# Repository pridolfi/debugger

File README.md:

# debugger
Simple JTAG debugger based on FT2232H.

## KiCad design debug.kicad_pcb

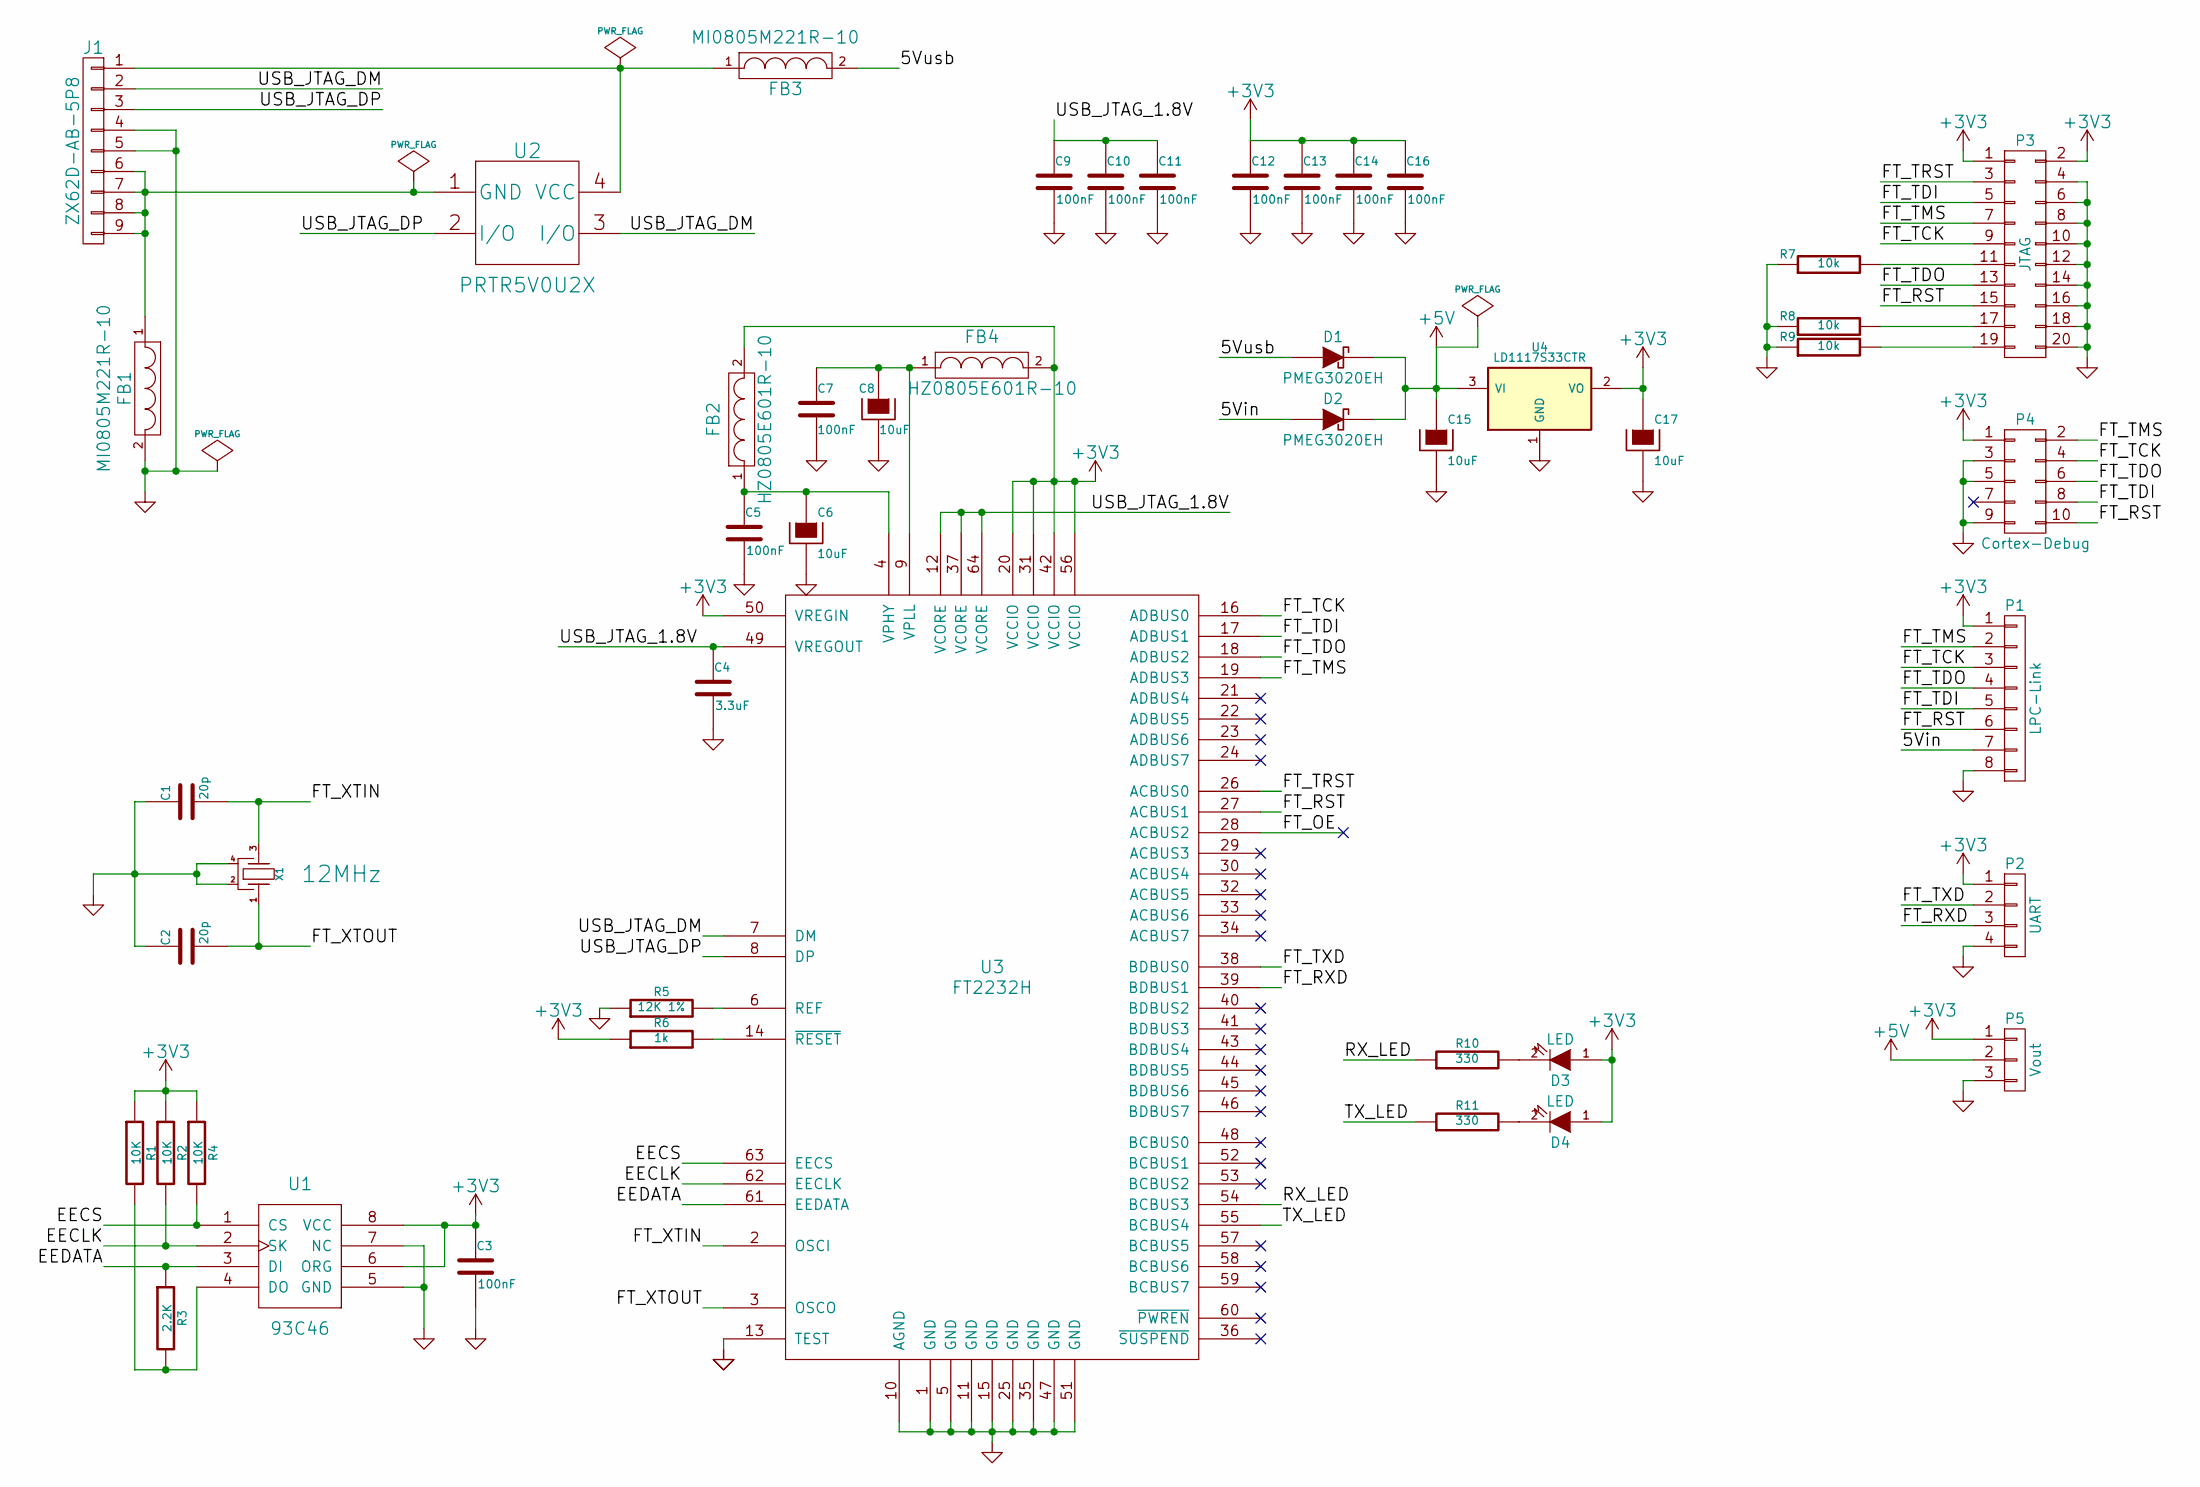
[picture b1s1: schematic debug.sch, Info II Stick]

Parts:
C1, C2: 20p; C_0805_HandSoldering; Digikey 399-8033-1-ND
C3, C5, C7, C9, C10, C11, C12, C13, C14, C16: 100nF; C_0805_HandSoldering; Digikey 399-1167-1-ND
C4: 3.3uF; C_0805_HandSoldering; Digikey 445-7582-1-ND
C6, C8, C15, C17: 10uF; TantalC_SizeA_EIA-3216_HandSoldering; Digikey 399-3525-1-ND
D1, D2: PMEG3020EH; SOD-123
D3, D4: LED; LED-0805
FB1, FB3: MI0805M221R-10; C_0805_HandSoldering; Digikey 240-2392-1-ND
FB2, FB4: HZ0805E601R-10; C_0805_HandSoldering; Digikey 240-2399-1-ND
J1: ZX62D-AB-5P8; USB_microAB_ZX62-AB&B-5PA-11; Digikey H11494CT-ND
P1: LPC-Link; Pin_Header_Straight_1x08
P2: UART; Pin_Header_Straight_1x04
P3: JTAG; Pin_Header_Straight_2x10
P4: Cortex-Debug; Pin_Array_5x2_1.27mm_SMD
P5: Vout; Pin_Header_Straight_1x03
R1, R2, R4: 10K; R_0805_HandSoldering; Digikey P10KACT-ND
R3: 2.2K; R_0805_HandSoldering; Digikey RMCF0805JT2K20CT-ND
R5: 12K 1%; R_0805_HandSoldering; Digikey 311-12.0KCRCT-ND
R6: 1k; R_0805_HandSoldering; Digikey RR12P15.0KDCT-ND
R7, R8, R9: 10k; R_0805_HandSoldering; Digikey 311-12.0KCRCT-ND
R10, R11: 330; R_0805_HandSoldering; Digikey 311-12.0KCRCT-ND
U1: 93C46; -SOIC8; Digikey AT93C46DN-SH-TCT-ND
U2: PRTR5V0U2X; SOT-143B; Digikey 568-4140-1-ND
U3: FT2232H; LQFP64-M05; Digikey 768-1024-1-ND
U4: LD1117S33CTR; SOT223_Opendous
X1: 12MHz; FA238V-XTAL; Digikey/Mouser 887-1831-1-ND

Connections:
+3V3: C3.1, C12.1, C13.1, C14.1, C16.1, C17.1, D3.1 (A), D4.1 (A), FB2.2, FB4.2, P1.1, P2.1, P3.1, P3.2, P4.1, P5.1, R1.1, R2.1, R4.1, R6.1, U1.6 (ORG), U1.8 (VCC), U3.20 (VCCIO), U3.31 (VCCIO), U3.42 (VCCIO), U3.50 (VREGIN), U3.56 (VCCIO), U4.2 (VO)
+5V: C15.1, D1.2 (K), D2.2 (K), P5.2, U4.3 (VI)
/5Vin: D2.1 (A), P1.7
/5Vusb: D1.1 (A), FB3.2
/EECLK: R2.2, U1.2 (SK), U3.62 (EECLK)
/EECS: R4.2, U1.1 (CS), U3.63 (EECS)
/EEDATA: R3.1, U1.3 (DI), U3.61 (EEDATA)
/FT_OE: U3.28 (ACBUS2)
/FT_RST: P1.6, P3.15, P4.10, U3.27 (ACBUS1)
/FT_RXD: P2.3, U3.39 (BDBUS1)
/FT_TCK: P1.3, P3.9, P4.4, U3.16 (ADBUS0)
/FT_TDI: P1.5, P3.5, P4.8, U3.17 (ADBUS1)
/FT_TDO: P1.4, P3.13, P4.6, U3.18 (ADBUS2)
/FT_TMS: P1.2, P3.7, P4.2, U3.19 (ADBUS3)
/FT_TRST: P3.3, U3.26 (ACBUS0)
/FT_TXD: P2.2, U3.38 (BDBUS0)
/FT_XTIN: C1.2, U3.2 (OSCI), X1.3 (B)
/FT_XTOUT: C2.2, U3.3 (OSCO), X1.1 (A)
/RX_LED: R10.1, U3.54 (BCBUS3)
/TX_LED: R11.1, U3.55 (BCBUS4)
/USB_JTAG_1.8V: C4.1, C9.1, C10.1, C11.1, U3.12 (VCORE), U3.37 (VCORE), U3.49 (VREGOUT), U3.64 (VCORE)
/USB_JTAG_DM: J1.2, U2.3 (I/O), U3.7 (DM)
/USB_JTAG_DP: J1.3, U2.2 (I/O), U3.8 (DP)
GND: C1.1, C2.1, C3.2, C4.2, C5.2, C6.2, C7.2, C8.2, C9.2, C10.2, C11.2, C12.2, C13.2, C14.2, C15.2, C16.2, C17.2, FB1.2, J1.4, J1.5, P1.8, P2.4, P3.4, P3.6, P3.8, P3.10, P3.12, P3.14, P3.16, P3.18, P3.20, P4.3, P4.5, P4.9, P5.3, R5.1, R7.1, R8.1, R9.1, U1.5 (GND), U1.7 (NC), U3.1 (GND), U3.5 (GND), U3.10 (AGND), U3.11 (GND), U3.13 (TEST), U3.15 (GND), U3.25 (GND), U3.35 (GND), U3.47 (GND), U3.51 (GND), U4.1 (GND), X1.2 (GND), X1.4 (GND)
unnamed: C5.1, C6.1, FB2.1, U3.4 (VPHY)
unnamed: C7.1, C8.1, FB4.1, U3.9 (VPLL)
unnamed: D3.2 (K), R10.2
unnamed: D4.2 (K), R11.2
unnamed: FB1.1, J1.6, J1.7, J1.8, J1.9, U2.1 (GND)
unnamed: FB3.1, J1.1, U2.4 (VCC)
unnamed: P3.11, R7.2
unnamed: P3.17, R8.2
unnamed: P3.19, R9.2
unnamed: R1.2, R3.2, U1.4 (DO)
unnamed: R5.2, U3.6 (REF)
unnamed: R6.2, U3.14 (~RESET)

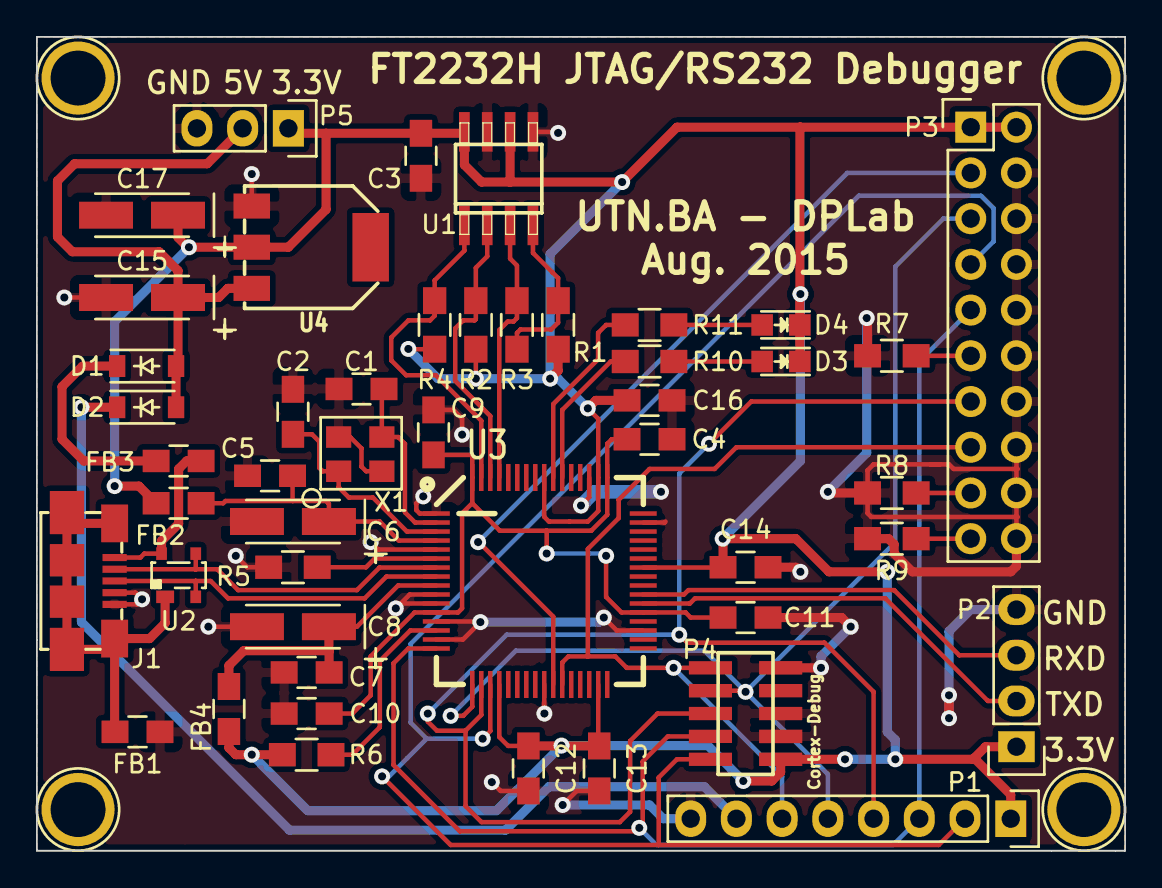
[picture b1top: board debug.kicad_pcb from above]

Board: 2 copper layers, 60.5 x 45.2 mm, 51 parts (0 on the bottom side), 35 nets.

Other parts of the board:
P6, P7, P8, P9: MH; 1pin

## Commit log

2015-08-24 commit inicial, esquematico terminado
2015-08-24 sch mejorado, erc ok, netlist generado
2015-08-25 working on footprint association
2015-08-26 footprint assoc done, working on placement
2015-08-26 place and route in progress...
2015-08-26 routing
2015-08-27 falta plano gnd
2015-08-28 pcb terminado, enviado a fabricacion
2015-09-29 added render image
2015-09-29 sch updated
